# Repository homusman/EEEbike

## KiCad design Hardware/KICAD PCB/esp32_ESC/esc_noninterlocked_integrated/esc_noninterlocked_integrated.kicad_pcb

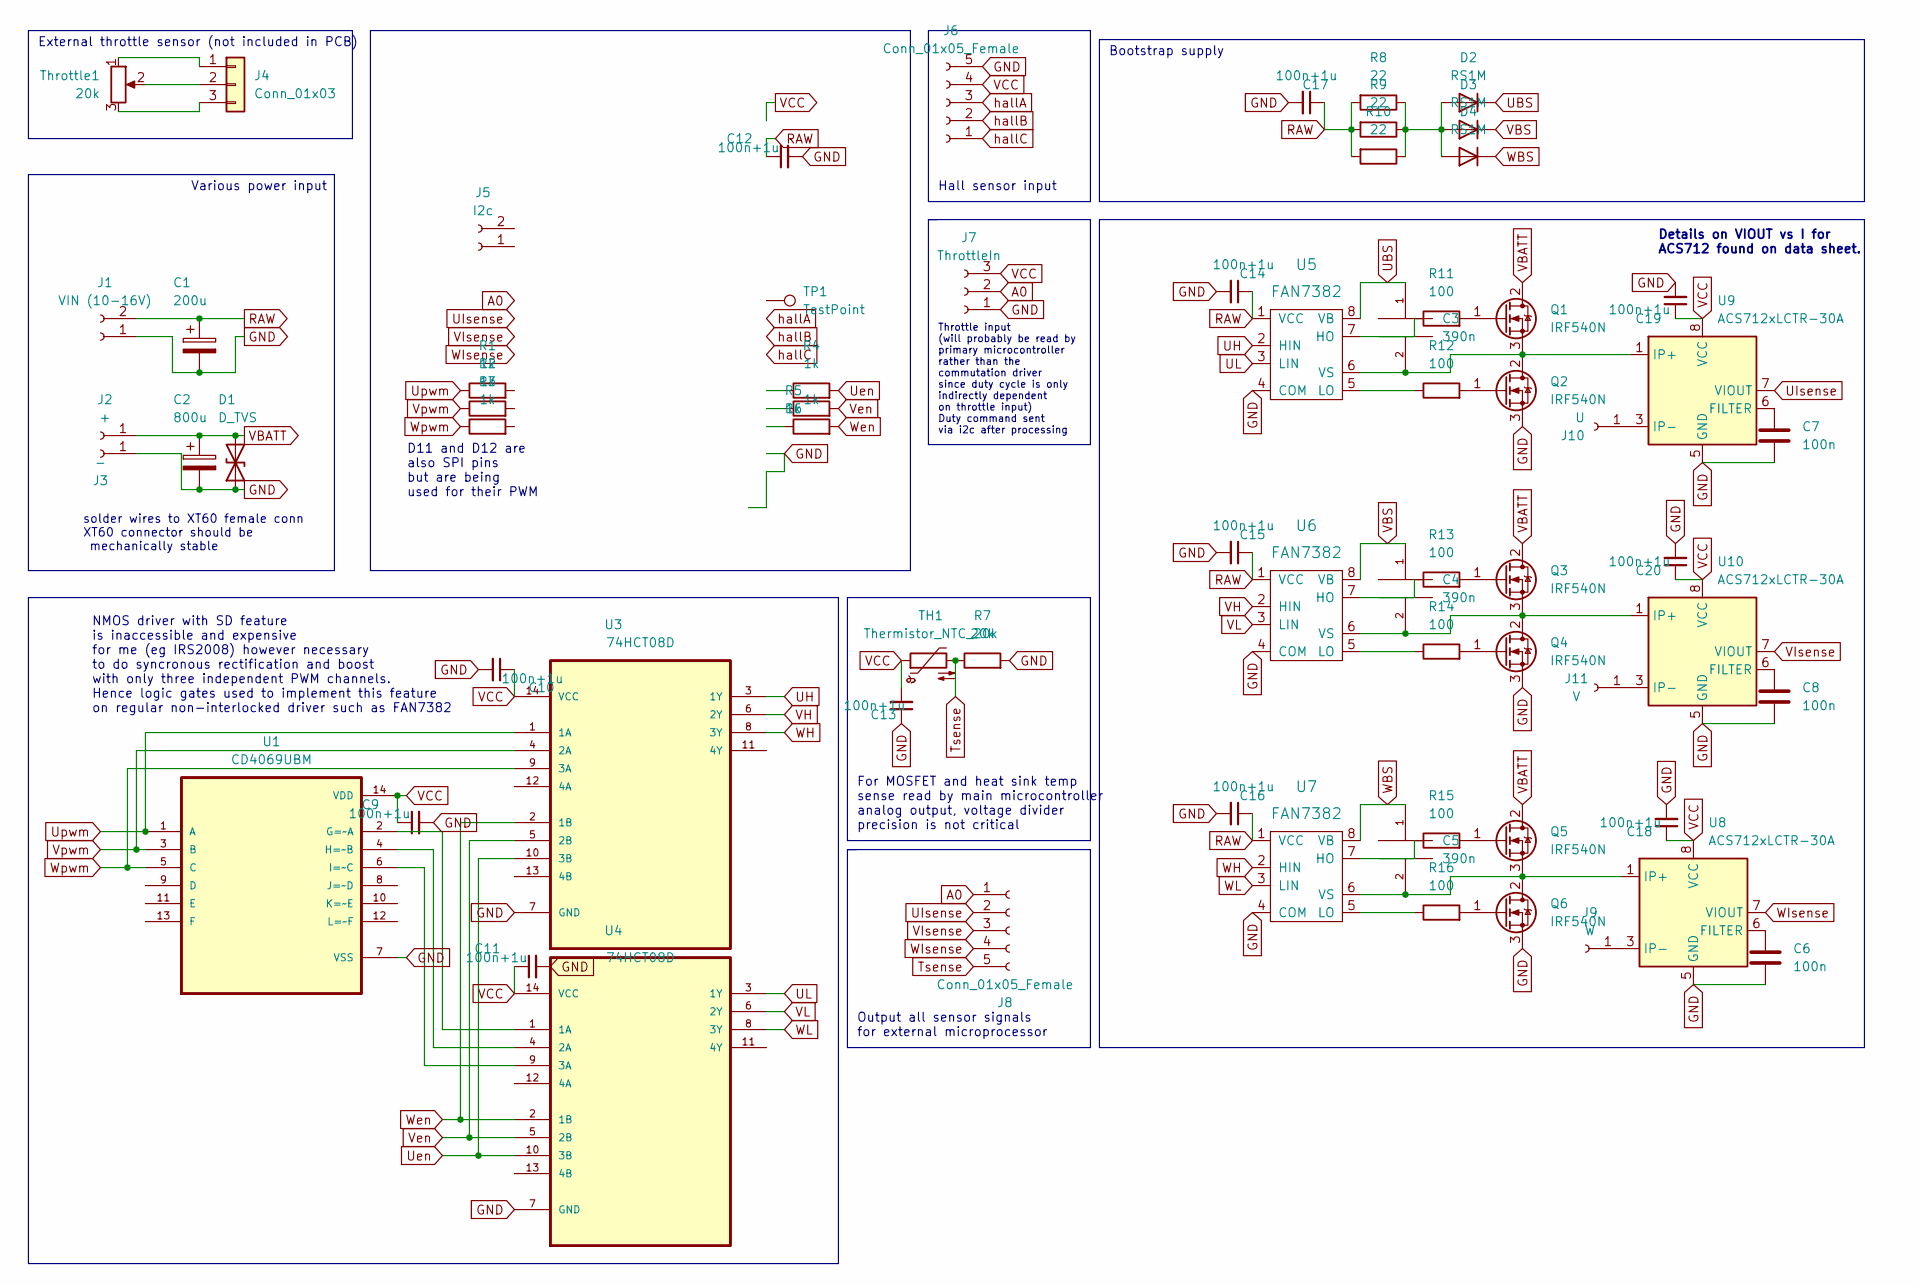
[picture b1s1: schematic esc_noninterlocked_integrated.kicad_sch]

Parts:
C1: 200u; CP_Radial_D8.0mm_P5.00mm
C2: 800u; CP_Axial_L10.0mm_D4.5mm_P15.00mm_Horizontal
C3, C4, C5: 390n; C_Rect_L7.0mm_W4.5mm_P5.00mm
C6, C7, C8: 100n; C_0603_1608Metric_Pad1.08x0.95mm_HandSolder
C9, C10, C11, C12, C13, C14, C15, C16, C17, C18, C19, C20: 100n+1u; Dual Capacitor SMD 0603 and 0805_HandSolder
D1: D_TVS; D_0805_2012Metric_Pad1.15x1.40mm_HandSolder
D2, D3, D4: RS1M; D_3220_8050Metric_Pad2.65x5.15mm_HandSolder
J1: VIN (10-16V); JST_EH_B2B-EH-A_1x02_P2.50mm_Vertical
J2: +; TestPoint_Loop_D3.80mm_Drill2.5mm
J3: -; TestPoint_Loop_D3.80mm_Drill2.5mm
J4: Conn_01x03; JST_EH_B3B-EH-A_1x03_P2.50mm_Vertical
J5: I2c; JST_EH_B2B-EH-A_1x02_P2.50mm_Vertical
J6, J8: Conn_01x05_Female; JST_EH_B5B-EH-A_1x05_P2.50mm_Vertical
J7: ThrottleIn; JST_EH_B3B-EH-A_1x03_P2.50mm_Vertical
J9: W; TestPoint_Loop_D3.80mm_Drill2.5mm
J10: U; TestPoint_Loop_D3.80mm_Drill2.5mm
J11: V; TestPoint_Loop_D3.80mm_Drill2.5mm
Q1, Q2, Q3, Q4, Q5, Q6: IRF540N; TO-220-3_Horizontal_TabUp_NoHoleClearance
R1, R2, R3, R4, R5, R6: 1k; R_1206_3216Metric_Pad1.30x1.75mm_HandSolder
R7: 20k; R_0805_2012Metric_Pad1.20x1.40mm_HandSolder
R8, R9, R10: 22; R_0805_2012Metric_Pad1.20x1.40mm_HandSolder
R11, R12, R13, R14, R15, R16: 100; R_1206_3216Metric_Pad1.30x1.75mm_HandSolder
TH1: Thermistor_NTC_20k; R_Axial_DIN0204_L3.6mm_D1.6mm_P1.90mm_Vertical
TP1: TestPoint; TestPoint_Loop_D1.80mm_Drill1.0mm_Beaded
Throttle1: 20k
U1: CD4069UBM; SOIC127P600X175-14N
U3, U4: 74HCT08D; SOIC127P600X175-14N; MPN 74HCT08D
U5, U6, U7: FAN7382; DIP762W52P254L1016H469Q8
U8, U9, U10: ACS712xLCTR-30A; SOIC-8_3.9x4.9mm_P1.27mm

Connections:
A0: J7.2, J8.1; also elsewhere on the board
GND: C1.2, C2.2, C6.2, C7.2, C8.2, C9.2, C10.2, C11.2, C12.2, C13.1, C14.2, C15.2, C16.2, C17.2, C18.2, C19.2, C20.2, D1.1 (A1), J1.1, J3.1, J6.5, J7.1, Q2.3 (S), Q4.3 (S), Q6.3 (S), R7.2, U1.7 (VSS), U3.7 (GND), U4.7 (GND), U5.4 (COM), U6.4 (COM), U7.4 (COM), U8.5 (GND), U9.5 (GND), U10.5 (GND); also elsewhere on the board
unnamed: C3.2, Q1.3 (S), Q2.2 (D), U5.6 (VS), U9.1 (IP+), U9.2 (IP+)
unnamed: C4.2, Q3.3 (S), Q4.2 (D), U6.6 (VS), U10.1 (IP+), U10.2 (IP+)
unnamed: C5.2, Q5.3 (S), Q6.2 (D), U7.6 (VS), U8.1 (IP+), U8.2 (IP+)
unnamed: C6.1, U8.6 (FILTER)
unnamed: C7.1, U9.6 (FILTER)
unnamed: C8.1, U10.6 (FILTER)
unnamed: D2.2 (A), D3.2 (A), D4.2 (A), R8.1, R9.1, R10.1
unnamed: J4.1, Throttle1.1
unnamed: J4.2, Throttle1.2
unnamed: J4.3, Throttle1.3
unnamed 12: J5.1; also elsewhere on the board
unnamed 13: J5.2; also elsewhere on the board
unnamed: J9.1, U8.3 (IP-), U8.4 (IP-)
unnamed: J10.1, U9.3 (IP-), U9.4 (IP-)
unnamed: J11.1, U10.3 (IP-), U10.4 (IP-)
unnamed: Q1.1 (G), R11.2
unnamed: Q2.1 (G), R12.2
unnamed: Q3.1 (G), R13.2
unnamed: Q4.1 (G), R14.2
unnamed: Q5.1 (G), R15.2
unnamed: Q6.1 (G), R16.2
unnamed 23: R1.2; also elsewhere on the board
unnamed 24: R2.2; also elsewhere on the board
unnamed 25: R3.2; also elsewhere on the board
unnamed 26: R4.1; also elsewhere on the board
unnamed 27: R5.1; also elsewhere on the board
unnamed 28: R6.1; also elsewhere on the board
unnamed: R11.1, U5.7 (HO)
unnamed: R12.1, U5.5 (LO)
unnamed: R13.1, U6.7 (HO)
unnamed: R14.1, U6.5 (LO)
unnamed: R15.1, U7.7 (HO)
unnamed: R16.1, U7.5 (LO)
unnamed 35: TP1.1; also elsewhere on the board
unnamed: U1.2 (G=~A), U4.1 (1A)
unnamed: U1.4 (H=~B), U4.4 (2A)
unnamed: U1.6 (I=~C), U4.9 (3A)
RAW: C1.1, C12.1, C14.1, C15.1, C16.1, C17.1, J1.2, R8.2, R9.2, R10.2, U5.1 (VCC), U6.1 (VCC), U7.1 (VCC); also elsewhere on the board
Tsense: J8.5, R7.1, TH1.2
UBS: C3.1, D2.1 (K), U5.8 (VB)
UH: U3.3 (1Y), U5.2 (HIN)
UIsense: J8.2, U9.7 (VIOUT); also elsewhere on the board
UL: U4.3 (1Y), U5.3 (LIN)
Uen: R4.2, U3.10 (3B), U4.10 (3B)
Upwm: R1.1, U1.1 (A), U3.1 (1A)
VBATT: C2.1, D1.2 (A2), J2.1, Q1.2 (D), Q3.2 (D), Q5.2 (D)
VBS: C4.1, D3.1 (K), U6.8 (VB)
VCC: C9.1, C10.1, C11.1, C13.2, C18.1, C19.1, C20.1, J6.4, J7.3, TH1.1, U1.14 (VDD), U3.14 (VCC), U4.14 (VCC), U8.8 (VCC), U9.8 (VCC), U10.8 (VCC); also elsewhere on the board
VH: U3.6 (2Y), U6.2 (HIN)
VIsense: J8.3, U10.7 (VIOUT); also elsewhere on the board
VL: U4.6 (2Y), U6.3 (LIN)
Ven: R5.2, U3.5 (2B), U4.5 (2B)
Vpwm: R2.1, U1.3 (B), U3.4 (2A)
WBS: C5.1, D4.1 (K), U7.8 (VB)
WH: U3.8 (3Y), U7.2 (HIN)
WIsense: J8.4, U8.7 (VIOUT); also elsewhere on the board
WL: U4.8 (3Y), U7.3 (LIN)
Wen: R6.2, U3.2 (1B), U4.2 (1B)
Wpwm: R3.1, U1.5 (C), U3.9 (3A)
hallA: J6.3; also elsewhere on the board
hallB: J6.2; also elsewhere on the board
hallC: J6.1; also elsewhere on the board

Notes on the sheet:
Hall sensor input
D11 and D12 are also SPI pins but are being used for their PWM
Throttle input (will probably be read by primary microcontroller rather than the commutation driver since duty cycle is only indirectly dependent on throttle input) Duty command sent via i2c after processing
Output all sensor signals for external microprocessor
solder wires to XT60 female conn XT60 connector should be mechanically stable
For MOSFET and heat sink temp sense read by main microcontroller analog output, voltage divider precision is not critical
Bootstrap supply
External throttle sensor (not included in PCB)
Details on VIOUT vs I for ACS712 found on data sheet.
Various power input
NMOS driver with SD feature is inaccessible and expensive for me (eg IRS2008) however necessary to do syncronous rectification and boost with only three independent PWM channels. Hence logic gates used to implement this feature on regular non-interlocked driver such as FAN7382

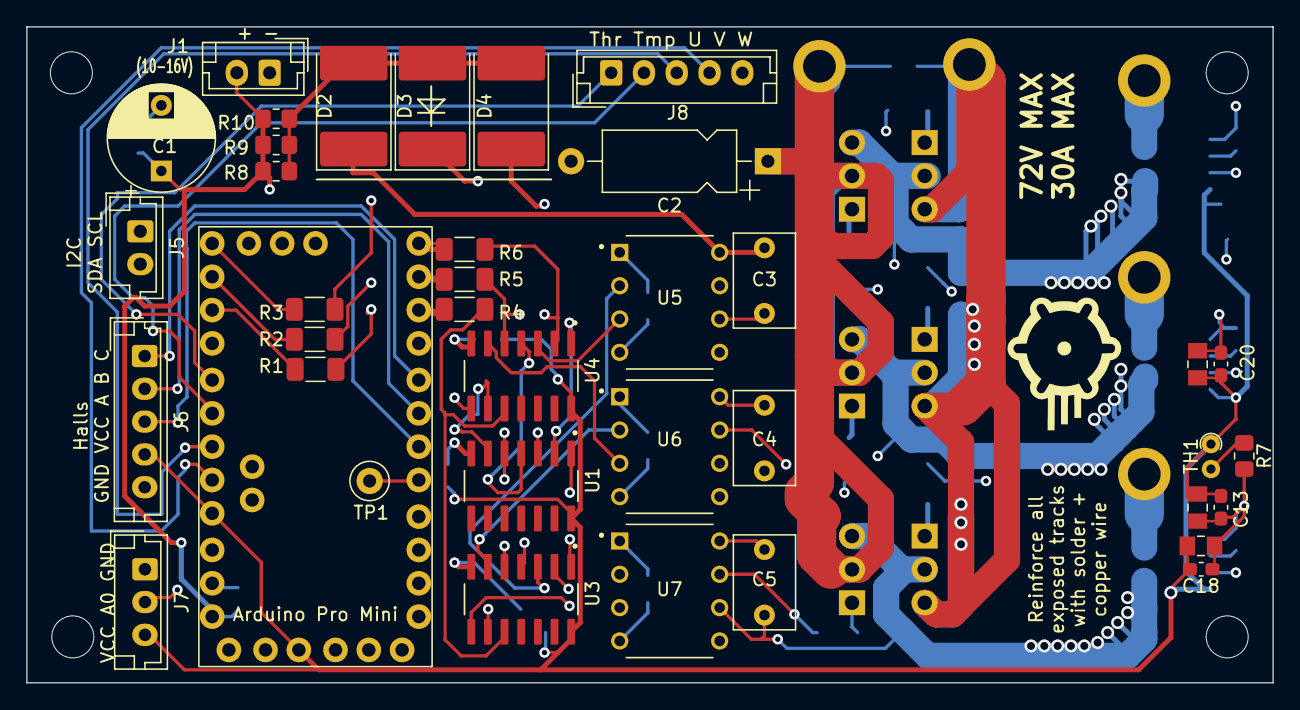
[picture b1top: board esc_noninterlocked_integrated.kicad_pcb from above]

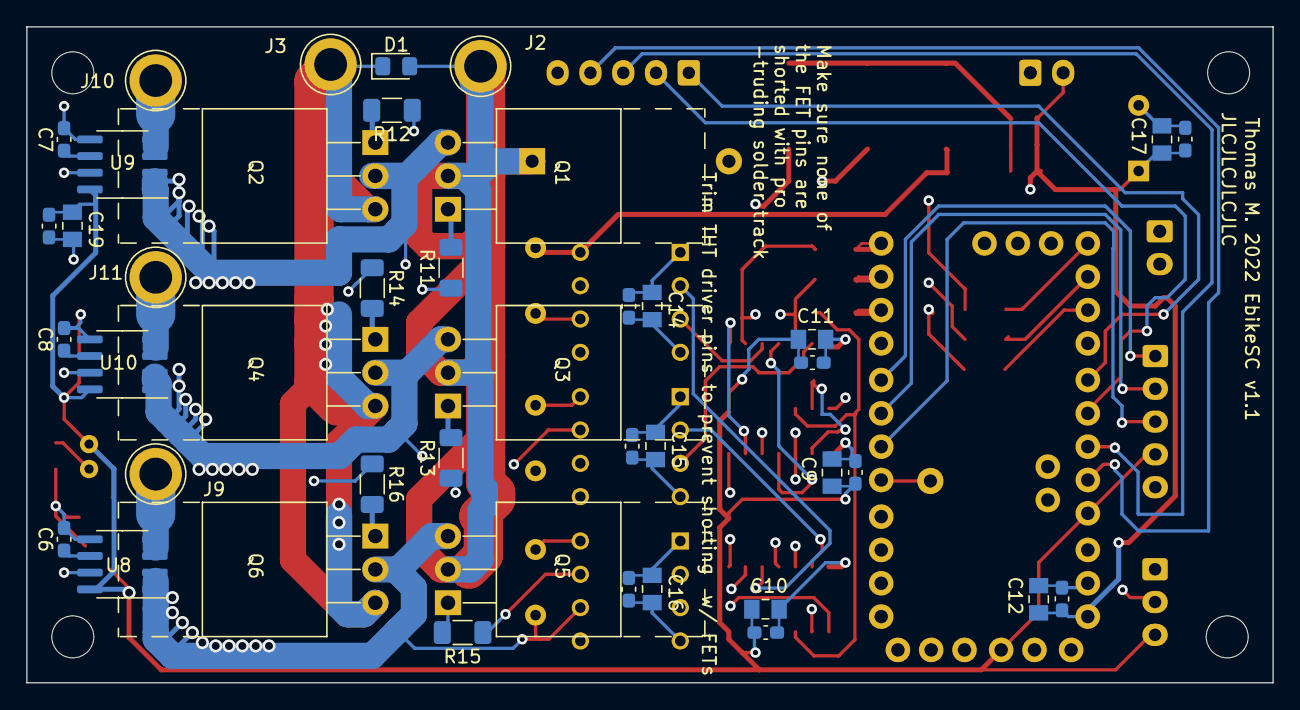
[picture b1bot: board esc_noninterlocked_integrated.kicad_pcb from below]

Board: 4 copper layers, 95.0 x 50.0 mm, 68 parts (33 on the bottom side), 61 nets.

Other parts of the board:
U2: ARDUINO_PRO_MINI; ARDUINO_PRO_MINI_ALIEXPRESS

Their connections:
A0: U2.18 (A0); also elsewhere on the board
GND: U2.5 (GND), U2.6 (GND), U2.12 (GND_1), U2.31 (GND_2), U2.35 (GND); also elsewhere on the board
unnamed 12: U2.8 (A5); also elsewhere on the board
unnamed 13: U2.7 (A4); also elsewhere on the board
unnamed 23: U2.20 (MISO); also elsewhere on the board
unnamed 24: U2.21 (MOSI); also elsewhere on the board
unnamed 25: U2.22 (D10); also elsewhere on the board
unnamed 26: U2.25 (D7); also elsewhere on the board
unnamed 27: U2.24 (D8); also elsewhere on the board
unnamed 28: U2.23 (D9); also elsewhere on the board
unnamed 35: U2.30 (D2); also elsewhere on the board
RAW: U2.11 (RAW); also elsewhere on the board
UIsense: U2.17 (A1); also elsewhere on the board
VCC: U2.4 (VCC), U2.14 (VCC_1); also elsewhere on the board
VIsense: U2.16 (A2); also elsewhere on the board
WIsense: U2.15 (A3); also elsewhere on the board
hallA: U2.29 (D3); also elsewhere on the board
hallB: U2.28 (D4); also elsewhere on the board
hallC: U2.27 (D5); also elsewhere on the board

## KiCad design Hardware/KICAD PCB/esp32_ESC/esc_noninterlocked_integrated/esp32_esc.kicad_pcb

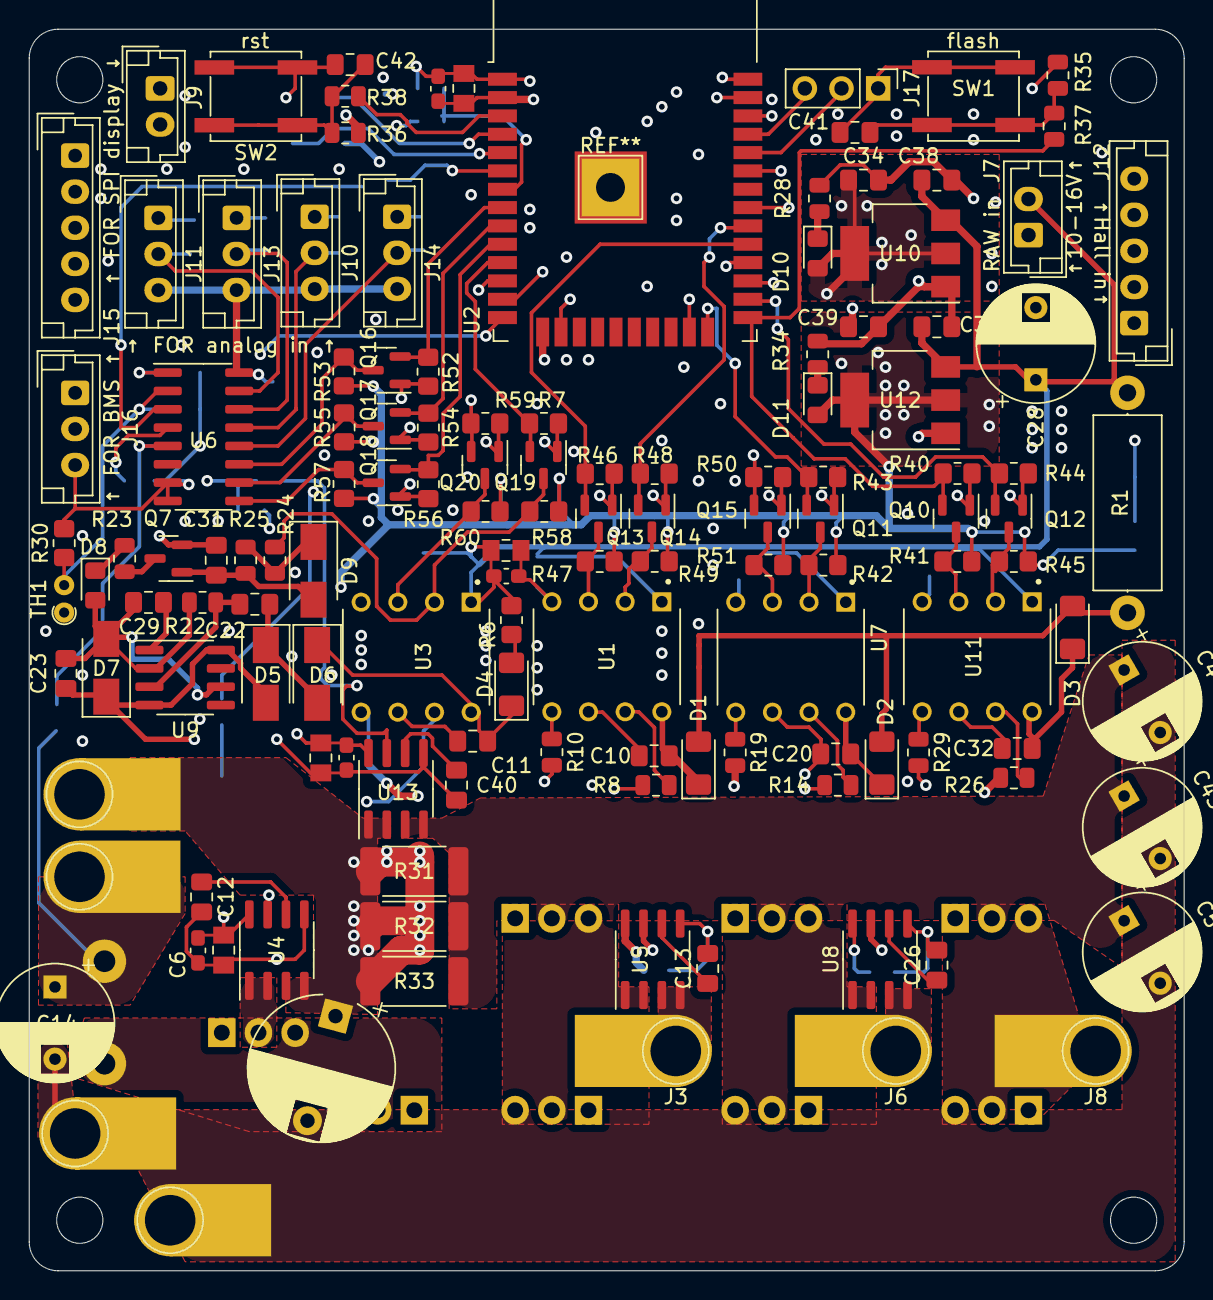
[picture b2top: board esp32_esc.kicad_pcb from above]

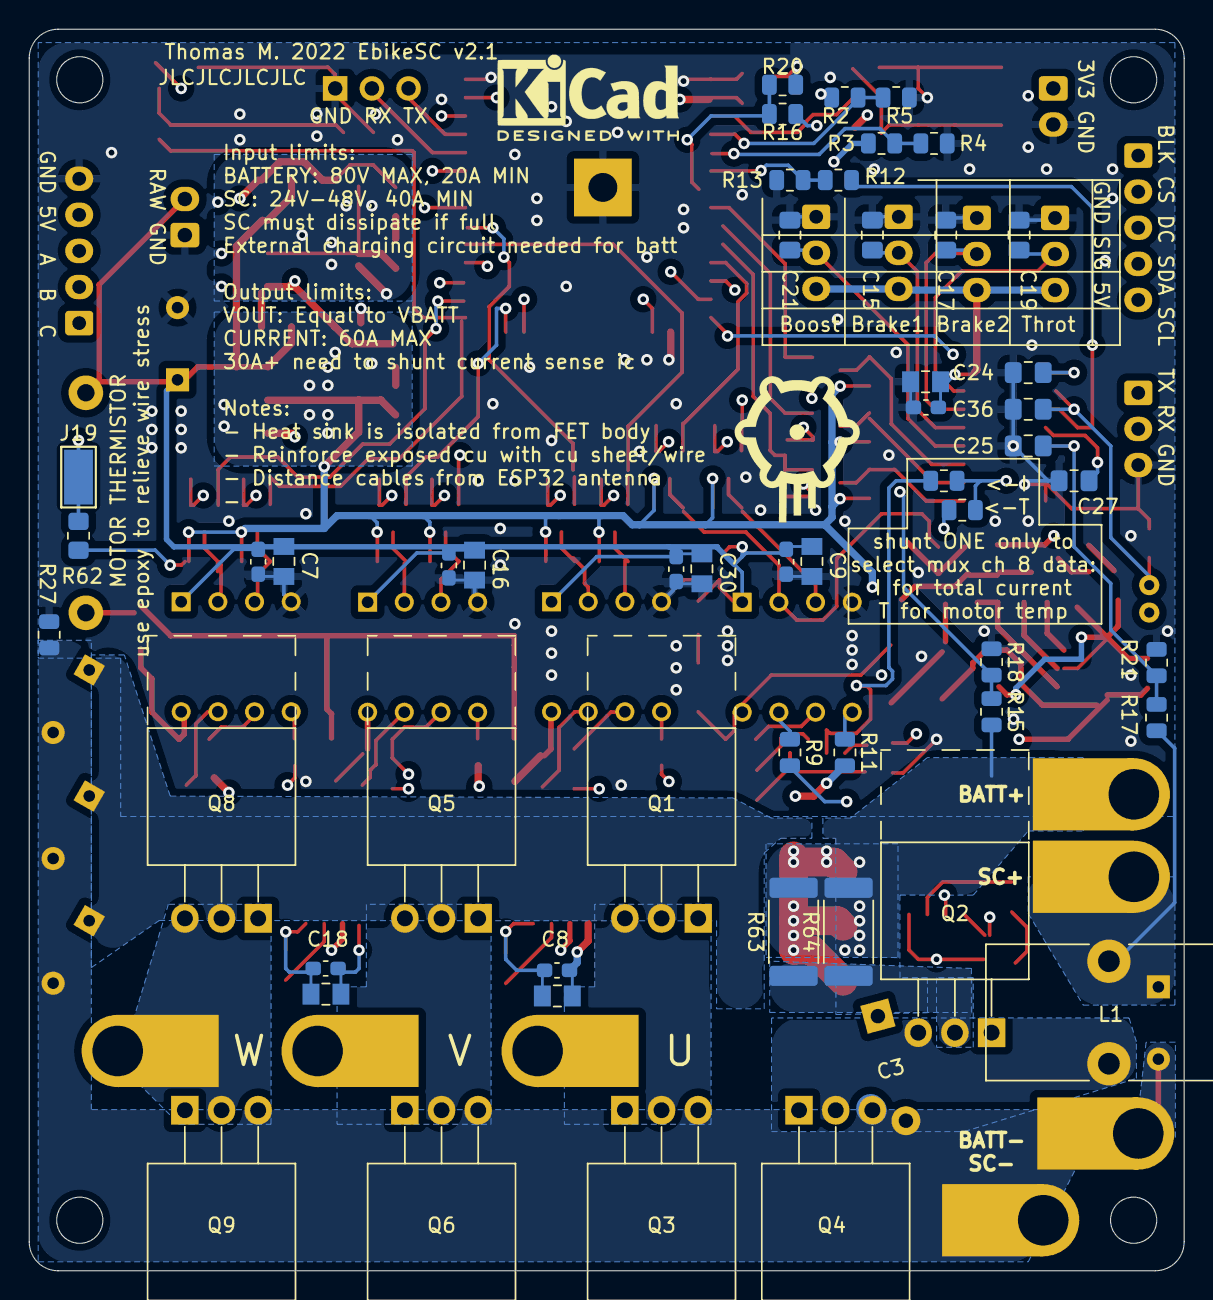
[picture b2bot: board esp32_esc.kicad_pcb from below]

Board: 4 copper layers, 80.0 x 86.0 mm, 173 parts (45 on the bottom side), 105 nets.

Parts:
C1, C2, C6, C7, C8, C9, C16, C18, C30, C35, C37: 100n; Dual Capacitor SMD 0603 and 0805_HandSolder
C3: 300u; CP_Radial_D10.0mm_P7.50mm
C4, C5, C14, C28, C43: 300u; CP_Radial_D8.0mm_P5.00mm
C10, C11, C20, C32: 390n; C_0805_2012Metric_Pad1.18x1.45mm_HandSolder
C12, C13, C15, C17, C19, C21, C24, C25, C26, C27, C31, C36, C40, C41, C42: 100n; C_0805_2012Metric_Pad1.18x1.45mm_HandSolder
C22: 20n; C_0805_2012Metric_Pad1.18x1.45mm_HandSolder
C23: 1u; C_0805_2012Metric_Pad1.18x1.45mm_HandSolder
C29: 1nf; C_0805_2012Metric_Pad1.18x1.45mm_HandSolder
C33, C34, C38, C39: 22u; C_0805_2012Metric_Pad1.18x1.45mm_HandSolder
D1, D2, D3, D4: RS1M; D_1206_3216Metric_Pad1.42x1.75mm_HandSolder
D5, D6, D9: SS14; D_SMA
D7: Zener12; D_SMA
D8, D10, D11: GREENLED; D_0805_2012Metric_Pad1.15x1.40mm_HandSolder
J1: BatteryIn+; TestPoint_Plated_Hole_D3.5mm
J2: BatteryIn-; TestPoint_Plated_Hole_D3.5mm
J3: U; TestPoint_Plated_Hole_D3.5mm
J4: SCIn+ (24-48V); TestPoint_Plated_Hole_D3.5mm
J5: SCIn-; TestPoint_Plated_Hole_D3.5mm
J6: V; TestPoint_Plated_Hole_D3.5mm
J7: VIN (10-16V); JST_EH_B2B-EH-A_1x02_P2.50mm_Vertical
J8: W; TestPoint_Plated_Hole_D3.5mm
J9: dispPwr; JST_EH_B2B-EH-A_1x02_P2.50mm_Vertical
J10: brake1; JST_EH_B3B-EH-A_1x03_P2.50mm_Vertical
J11: throttle; JST_EH_B3B-EH-A_1x03_P2.50mm_Vertical
J12: hall; JST_EH_B5B-EH-A_1x05_P2.50mm_Vertical
J13: brake2; JST_EH_B3B-EH-A_1x03_P2.50mm_Vertical
J14: boost; JST_EH_B3B-EH-A_1x03_P2.50mm_Vertical
J15: dispSPI; JST_EH_B5B-EH-A_1x05_P2.50mm_Vertical
J16: BMS; JST_EH_B3B-EH-A_1x03_P2.50mm_Vertical
J17: UART; PinHeader_1x03_P2.54mm_Vertical
J19: Conn_01x01_Female; TestPoint_Keystone_5019_Minature
L1: 4u; L_Toroid_Vertical_L16.8mm_W9.2mm_P7.10mm_Vishay_TJ3_BigPads
Q1, Q2, Q3, Q4, Q5, Q6, Q8, Q9: IRF3710; TO-220-3_Horizontal_TabUp_NoHoleClearance
Q7, Q10, Q11, Q12, Q13, Q14, Q15, Q16, Q17, Q18, Q19, Q20: 2N7002; SOT-23
R1: 10; R_Axial_DIN0414_L11.9mm_D4.5mm_P15.24mm_Horizontal
R2, R3, R12, R16: 1k; R_0805_2012Metric
R4, R5, R13, R20: 2k; R_0805_2012Metric
R6: 47; R_0805_2012Metric_Pad1.20x1.40mm_HandSolder
R7, R40, R41, R42, R43, R44, R45, R46, R47, R48, R49, R50, R51, R52, R53, R54, R55, R56, R57, R58, R59, R60: 10k; R_0805_2012Metric_Pad1.20x1.40mm_HandSolder
R8, R10, R14, R19, R26, R29: 100; R_0805_2012Metric
R9, R11: 40; R_0805_2012Metric
R15: 200k; R_0805_2012Metric
R17: 100k; R_0805_2012Metric
R18, R21: 10k; R_0805_2012Metric
R22: 47k; R_0805_2012Metric
R23: 3400; R_0805_2012Metric
R24, R37, R38: 470; R_0805_2012Metric
R25, R35, R36: 4.7k; R_0805_2012Metric
R27, R39, R61: 10m; R_0805_2012Metric
R28: 260; R_0805_2012Metric
R30, R62: 20k; R_0805_2012Metric_Pad1.20x1.40mm_HandSolder
R31, R32, R33, R63, R64: 1.2m; R_2512_6332Metric_Pad1.40x3.35mm_HandSolder
R34: 600; R_0805_2012Metric
SW1, SW2: SW_MEC_5G; SW_SPST_EVPBF
TH1: Thermistor_NTC_20k; R_Axial_DIN0204_L3.6mm_D1.6mm_P1.90mm_Vertical
U1, U3, U7, U11: FAN7382; DIP762W52P254L1016H469Q8
U2: ESP32-WROOM-32
U4, U5, U8, U13: ACS712xLCTR-30A; SOIC-8_3.9x4.9mm_P1.27mm
U6: CD4051B; SOIC-16_3.9x9.9mm_P1.27mm
U9: LM555xM; SOIC-8_3.9x4.9mm_P1.27mm
U10: AMS1117-3.3; SOT-223-3_TabPin2
U12: AMS1117-5.0; SOT-223-3_TabPin2

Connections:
+3V3: C2.2, C34.1, D10.2 (A), J9.1, Q10.1 (G), Q11.1 (G), Q12.1 (G), Q13.1 (G), Q14.1 (G), Q15.1 (G), Q16.1 (G), Q17.1 (G), Q18.1 (G), Q19.1 (G), Q20.1 (G), R7.1, R35.2, R36.2, R40.1, R42.1, R44.1, R46.1, R48.1, R50.1, R52.1, R54.1, R56.1, R59.1, U2.2 (VDD), U10.2 (VO)
+5V: C6.1, C8.1, C18.1, C35.2, C37.2, C39.1, D11.2 (A), J10.3, J11.3, J12.4, J13.3, J14.3, R41.1, R43.1, R45.1, R47.1, R49.1, R51.1, R53.1, R55.1, R57.1, R58.1, R60.1, R62.2, TH1.1, U4.8 (VCC), U5.8 (VCC), U6.16 (VDD), U8.8 (VCC), U12.2 (VO), U13.8 (VCC)
/3V3to5V1/LIN: Q11.2 (S), R42.2, U2.24 (IO2)
/3V3to5V2/LIN: Q12.2 (S), R44.2, U2.26 (IO4)
/3V3to5V3/LIN: Q13.2 (S), R46.2, U2.29 (IO5)
/3V3to5V4/LIN: Q14.2 (S), R48.2, U2.30 (IO18)
/3V3to5V5/LIN: Q15.2 (S), R50.2, U2.37 (IO23)
/3V3to5V6/HIN: Q16.3 (D), R53.2, U6.11 (A)
/3V3to5V6/LIN: Q16.2 (S), R52.2, U2.8 (IO32)
/3V3to5V7/HIN: Q17.3 (D), R55.2, U6.10 (B)
/3V3to5V7/LIN: Q17.2 (S), R54.2, U2.9 (IO33)
/3V3to5V8/HIN: Q18.3 (D), R57.2, U6.9 (C)
/3V3to5V8/LIN: Q18.2 (S), R56.2, U2.10 (IO25)
/3V3to5V9/LIN: Q20.2 (S), R59.2, U2.12 (IO27)
/3V3to5V10/LIN: Q19.2 (S), R7.2, U2.11 (IO26)
CS: J15.2, U2.23 (IO15)
DC: J15.3, U2.14 (IO12)
EN: R38.1, U2.3 (EN)
GND: C1.2, C2.1, C6.2, C7.2, C8.2, C9.2, C12.2, C13.2, C15.1, C16.2, C17.1, C18.2, C19.1, C21.1, C24.1, C25.1, C26.2, C27.1, C28.2, C30.2, C33.2, C34.2, C35.1, C36.1, C37.1, C38.2, C39.2, C40.2, C41.1, C42.1, J7.1, J9.2, J10.1, J11.1, J12.5, J13.1, J14.1, J16.3, J17.1, R4.1, R5.1, R13.1, R18.1, R20.1, R21.1, R27.2, R28.1, R30.2, R34.1, SW1.2 (B), SW2.2 (B), U1.4 (COM), U2.1 (GND), U2.15 (GND), U2.38 (GND), U2.39 (GND), U3.4 (COM), U4.5 (GND), U5.5 (GND), U6.7 (VEE), U6.8 (VSS), U7.4 (COM), U8.5 (GND), U10.1 (GND), U11.4 (COM), U12.1 (GND), U13.5 (GND)
GNDPWR: C3.2, C4.2, C5.2, C14.2, C31.2, C43.2, J2.1, J5.1, Q3.3 (S), Q4.3 (S), Q6.3 (S), Q7.2 (S), Q9.3 (S), R27.1
IO0: Q10.2 (S), R37.1, R40.2, U2.25 (IO0)
I_Bsense: R16.2, U4.7 (VIOUT)
I_Usense: R3.1, U5.7 (VIOUT)
I_Vsense: R2.1, U8.7 (VIOUT)
I_totsense: R39.2, U13.7 (VIOUT)
unnamed: C10.2, Q1.3 (S), Q3.2 (D), U1.6 (VS), U5.1 (IP+), U5.2 (IP+)
unnamed: C12.1, U4.6 (FILTER)
unnamed: C13.1, U5.6 (FILTER)
unnamed: C20.2, Q5.3 (S), Q6.2 (D), U7.6 (VS), U8.1 (IP+), U8.2 (IP+)
unnamed: C22.1, D5.1 (K), D6.2 (A)
unnamed: C22.2, R22.1, U9.3 (Q)
unnamed: C23.2, C29.1, D7.2 (A), D8.2 (A), R22.2, U9.2 (TR), U9.6 (THR)
unnamed: C24.2, R15.1, R18.2, U6.1 (X4)
unnamed: C25.2, R17.1, R21.2, U6.5 (X5)
unnamed: C26.1, U8.6 (FILTER)
unnamed: C27.2, R39.1, R61.1, U6.4 (X7)
unnamed: C29.2, U9.1 (GND)
unnamed: C31.1, D9.2 (A), Q7.1 (G), R25.2
unnamed: C32.2, J8.1, Q8.3 (S), Q9.2 (D), U11.6 (VS)
unnamed: C40.1, U13.6 (FILTER)
unnamed: C41.2, R35.1, R37.2, SW1.1 (A)
unnamed: C42.2, R36.1, R38.2, SW2.1 (A)
unnamed: D1.2 (A), D2.2 (A), D3.2 (A), R1.1
unnamed: D4.2 (A), R6.1
unnamed: D8.1 (K), R23.1
unnamed: D9.1 (K), R24.2, R25.1
unnamed: D10.1 (K), R28.2
unnamed: D11.1 (K), R34.2
unnamed: J3.1, U5.3 (IP-), U5.4 (IP-)
unnamed: J6.1, U8.3 (IP-), U8.4 (IP-)
unnamed: J17.2, U2.34 (RXD0/IO3)
unnamed: J17.3, U2.35 (TXD0/IO1)
unnamed: Q1.1 (G), R8.2
unnamed: Q2.1 (G), R9.2
unnamed: Q2.2 (D), R63.1, R64.1, U4.1 (IP+), U4.2 (IP+)
unnamed: Q3.1 (G), R10.2
unnamed: Q4.1 (G), R11.2
unnamed: Q5.1 (G), R14.2
unnamed: Q6.1 (G), R19.2
unnamed: Q7.3 (D), R23.2
unnamed: Q8.1 (G), R26.2
unnamed: Q9.1 (G), R29.2
unnamed: R2.2, R5.2, U2.4 (SENSOR_VP)
unnamed: R3.2, R4.2, U2.5 (SENSOR_VN)
unnamed: R8.1, U1.7 (HO)
unnamed: R9.1, U3.7 (HO)
unnamed: R10.1, U1.5 (LO)
unnamed: R11.1, U3.5 (LO)
unnamed: R12.1, R13.2, U2.6 (IO34)
unnamed: R12.2, U6.3 (X)
unnamed: R14.1, U7.7 (HO)
unnamed: R16.1, R20.2, U2.7 (IO35)
unnamed: R19.1, U7.5 (LO)
unnamed: R26.1, U11.7 (HO)
unnamed: R29.1, U11.5 (LO)
RAW: C1.1, C7.1, C9.1, C16.1, C28.1, C30.1, C33.1, C38.1, J7.2, R1.2, R6.2, U1.1 (VCC), U3.1 (VCC), U7.1 (VCC), U10.3 (VI), U11.1 (VCC), U12.3 (VI)
RX_forbms: J16.2, U2.27 (IO16)
SCL: J15.5, U2.13 (IO14)
SDA: J15.4, U2.16 (IO13)
SR: Q19.3 (D), R24.1, R58.2, U3.2 (HIN)
SW: Q20.3 (D), R60.2, U3.3 (LIN)
TX_forbms: J16.1, U2.28 (IO17)
Tmotor: J19.1, R61.2, R62.1
Tsink: C36.2, R30.1, TH1.2, U6.2 (X6)
UBS: C10.1, D1.1 (K), U1.8 (VB)
UH: Q14.3 (D), R49.2, U1.2 (HIN)
UL: Q13.3 (D), R47.2, U1.3 (LIN)
VBS: C20.1, D2.1 (K), U7.8 (VB)
VBUS: C3.1, J1.1, R15.2, R31.1, R32.1, R33.1, R63.2, R64.2, U4.3 (IP-), U4.4 (IP-), U13.1 (IP+), U13.2 (IP+)
VH: Q11.3 (D), R43.2, U7.2 (HIN)
VL: Q15.3 (D), R51.2, U7.3 (LIN)
VMOTOR: C4.1, C5.1, C43.1, Q1.2 (D), Q5.2 (D), Q8.2 (D), R31.2, R32.2, R33.2, U13.3 (IP-), U13.4 (IP-)
VSC: C14.1, J4.1, L1.1, R17.2
Vs: C11.2, C23.1, D5.2 (A), D7.1 (K), L1.2, Q2.3 (S), Q4.2 (D), U3.6 (VS), U9.4 (R), U9.8 (VCC)
WBS: C32.1, D3.1 (K), U11.8 (VB)
WH: Q12.3 (D), R45.2, U11.2 (HIN)
WL: Q10.3 (D), R41.2, U11.3 (LIN)
boost: C21.2, J14.2, U6.12 (X3)
brake1: C15.2, J10.2, U6.13 (X0)
brake2: C17.2, J13.2, U6.14 (X1)
cp: C11.1, D4.1 (K), D6.1 (K), U3.8 (VB)
hallA: J12.3, U2.31 (IO19)
hallB: J12.2, U2.33 (IO21)
hallC: J12.1, U2.36 (IO22)
throttle: C19.2, J11.2, U6.15 (X2)

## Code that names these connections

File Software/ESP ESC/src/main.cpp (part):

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  #define PWMregenmaxval 178 //duty cycle at which power output is maximum based on adafruit calculator
  //boost controller outputs and their corresponding PWM channels

  #define SR 26//boost converter sychronous rectification switch output
  #define SW 27//boost converter low switch output

  #define SRch 7
  #define SWch 8

 //motor hall inputs
  #define hallA 19 
  #define hallB 21
  #define hallC 22

  //serial communication with BMS
  #define bmsRX 16
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  //current sensors
  #define IUSense 39
  #define IVSense 35
  #define IBSense 35//boost converter output current


//ESC behaviour config
#define PBattMax 1000*10^3//(mW) 
#define PBoostMax 2000*10^3//(mW)refers to max output/input power of boost converter at worst case, and is limited by max SC current at lowest SC voltage 
#define VBattMax 48*10^6//(uV)
#define VscMax 16*10^6//(uV)
#define VOvercharge 50*10^3//(uV) exceed defined maximum by this much to add some hysterisis and prevent bouncing between SC and batt recharge due to self discharge
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  int PBoostCommand; //(mW)

  //Measurements
  int Vbatt=0; //(uV)
  int Vsc=0; //(uV)
  int Tsink=0; //(mK)
  int Tmotor=0; //(mK)
  int Itot=0; //(uA)
  int Ibatt=0; //(uA)
  int Iboost=0; //(uA)
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  Consequentially the SC can be precharged by activating the brakes whilst also using the throttle as long as SC is not already full. 
  Because Iboost < 0 based on brake regen command and Ibatt > 0 based on throttle command*/
   //for IBoost
  PBoostCommand = 0;//clamp(map(boost,0,4095,0,PBoostMax),0,PBoostMax); TODO TEMPORARY FOR TESTING
  //for IBatt
  PBattCommand = clamp(map(throttle,0,4095,0,PBattMax),0,PBattMax); 

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

  //compute aggregate brake command
  brakeTot = 0;//clamp(brake1 + brake2,0,4095); TODO TEMPORARY FOR TESTING
  
  //raw regen power is mapped from aggregate brake cmd
  //0 regen command corresponds to both brakes at rest, when either brake is fully squeezed (ie 4095) max power output is commanded (equal to PSC max)
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Tmotor = analogReadMilliVolts(muxIn);
#elif multiplxCh8 == 2
/* MOVED TO readCurrent 
Tmotor = 0;
Itot = Itot*weight1+weight*(analogReadMilliVolts(muxIn)-Itotrest)*ISenseScalar;
Itot = Itot/(weight1+weight);
*/
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pinMode(muxB,OUTPUT);
pinMode(muxC,OUTPUT);

pinMode(hallA,INPUT_PULLUP);
pinMode(hallB,INPUT_PULLUP);
pinMode(hallC,INPUT_PULLUP);

pinMode(IUSense,INPUT);
pinMode(IVSense,INPUT);
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
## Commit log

2023-04-12 Initial commit
    Moved all of my previously local files to github for version control
